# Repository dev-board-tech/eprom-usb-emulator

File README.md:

# eprom-usb-emulator
 A USB EPROM EEPROM RAM emulator

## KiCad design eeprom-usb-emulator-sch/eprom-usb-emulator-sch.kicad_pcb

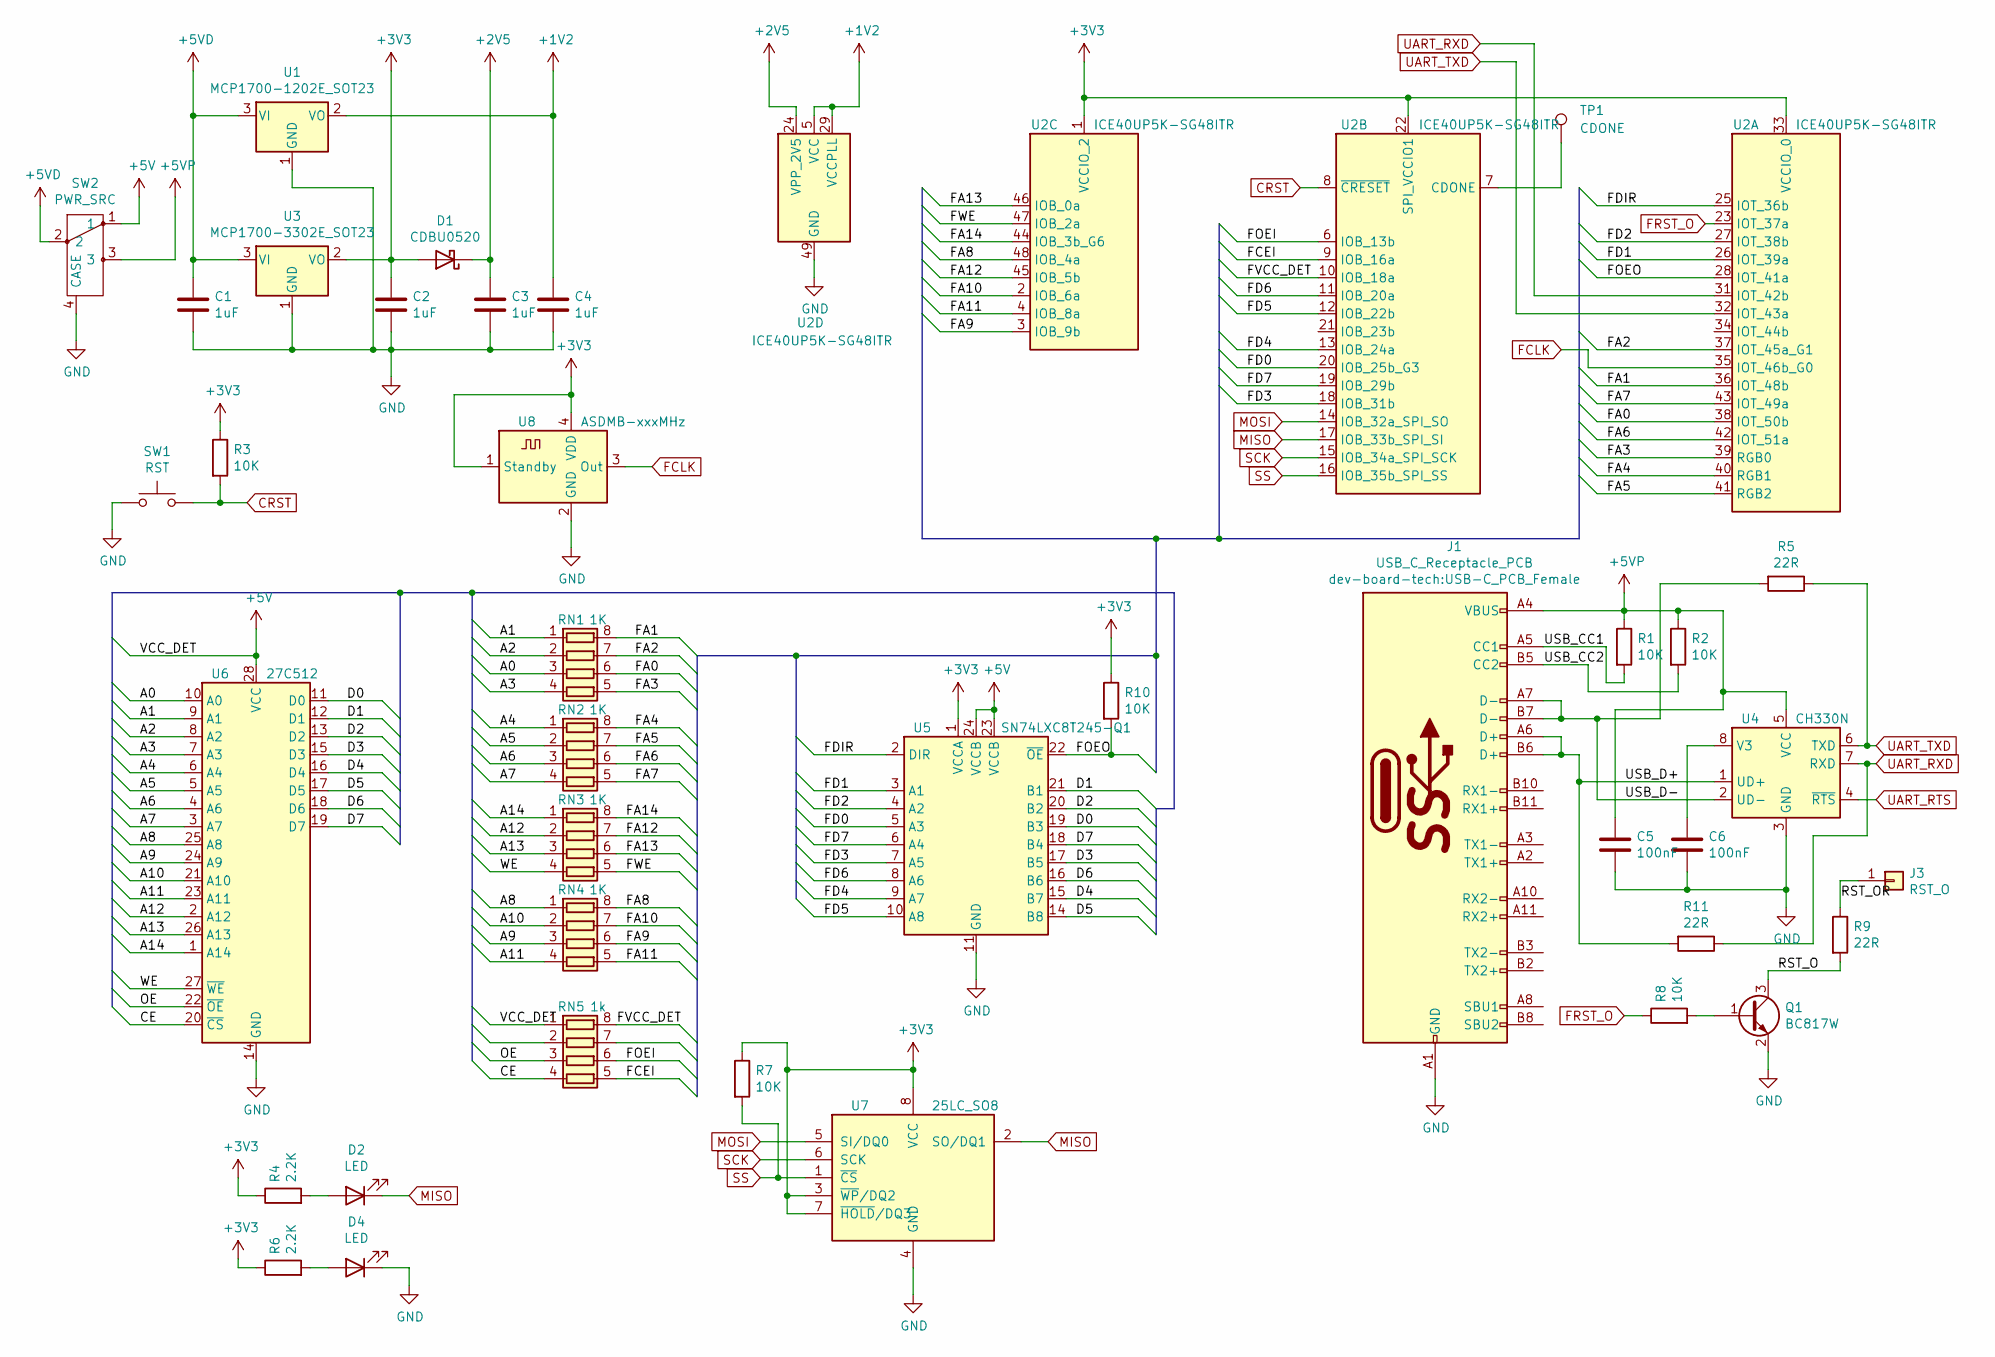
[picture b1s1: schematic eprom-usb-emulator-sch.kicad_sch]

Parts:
C1, C2, C3, C4: 1uF; C_0805_2012Metric
C5, C6: 100nF; C_0603_1608Metric
D1: CDBU0520; D_SOD-523
D2, D4: LED; LED_0603_1608Metric
J1: USB_C_Receptacle_PCB; USB-C_PCB_Female
J3: RST_O; PinHeader_1x01_P2.54mm_Vertical
Q1: BC817W; SOT-323_SC-70
R1, R2, R3, R7, R8, R10: 10K; R_0603_1608Metric
R4, R6: 2.2K; R_0603_1608Metric
R5, R11: 22R; R_0402_1005Metric
R9: 22R; R_1206_3216Metric
RN1, RN2, RN3, RN4: 1K; R_Array_Convex_4x0402
RN5: 1k; R_Array_Convex_4x0402
SW1: RST; SW_SPST_CK_RS282G05A3
SW2: PWR_SRC; SW_SPDT_PCM12
TP1: CDONE; TestPoint_Pad_D1.0mm
U1: MCP1700-1202E_SOT23; SOT-23
U2: ICE40UP5K-SG48ITR; QFN-48-1EP_7x7mm_P0.5mm_EP5.6x5.6mm
U3: MCP1700-3302E_SOT23; SOT-23
U4: CH330N; SOIC-8_3.9x4.9mm_P1.27mm
U5: SN74LXC8T245-Q1; TSSOP-24_4.4x7.8mm_P0.65mm
U6: 27C512; 28PIN_EPROM_EMULATOR_DIP-28_W15.24mm
U7: 25LC_SO8; SOIC-8_3.9x4.9mm_P1.27mm
U8: ASDMB-xxxMHz; Oscillator_SMD_Abracon_ASDMB-4Pin_2.5x2.0mm

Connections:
+1V2: C4.1, U1.2 (VO), U2.5 (VCC), U2.29 (VCCPLL), U2.30 (VCC)
+2V5: C3.1, D1.1 (K), U2.24 (VPP_2V5)
+3V3: C2.1, D1.2 (A), R3.1, R4.1, R6.1, R7.1, R10.1, U2.1 (VCCIO_2), U2.22 (SPI_VCCIO1), U2.33 (VCCIO_0), U3.2 (VO), U5.1 (VCCA), U7.3 (~WP/DQ2), U7.7 (~HOLD/DQ3), U7.8 (VCC), U8.1 (Standby), U8.4 (VDD)
+5V: RN5.1 (R1.1), SW2.1, U5.23 (VCCB), U5.24 (VCCB), U6.28 (VCC)
+5VD: C1.1, SW2.2, U1.3 (VI), U3.3 (VI)
+5VP: C5.1, J1.A4 (VBUS), J1.A9 (VBUS), J1.B4 (VBUS), J1.B9 (VBUS), R1.1, R2.1, SW2.3, U4.5 (VCC)
/A0: RN1.3 (R3.1), U6.10 (A0)
/A1: RN1.1 (R1.1), U6.9 (A1)
/A2: RN1.2 (R2.1), U6.8 (A2)
/A3: RN1.4 (R4.1), U6.7 (A3)
/A4: RN2.1 (R1.1), U6.6 (A4)
/A5: RN2.2 (R2.1), U6.5 (A5)
/A6: RN2.3 (R3.1), U6.4 (A6)
/A7: RN2.4 (R4.1), U6.3 (A7)
/A8: RN4.1 (R1.1), U6.25 (A8)
/A9: RN4.3 (R3.1), U6.24 (A9)
/A10: RN4.2 (R2.1), U6.21 (A10)
/A11: RN4.4 (R4.1), U6.23 (A11)
/A12: RN3.2 (R2.1), U6.2 (A12)
/A13: RN3.3 (R3.1), U6.26 (A13)
/A14: RN3.1 (R1.1), U6.1 (A14)
/CE: RN5.4 (R4.1), U6.20 (~CS)
/D0: U5.19 (B3), U6.11 (D0)
/D1: U5.21 (B1), U6.12 (D1)
/D2: U5.20 (B2), U6.13 (D2)
/D3: U5.17 (B5), U6.15 (D3)
/D4: U5.15 (B7), U6.16 (D4)
/D5: U5.14 (B8), U6.17 (D5)
/D6: U5.16 (B6), U6.18 (D6)
/D7: U5.18 (B4), U6.19 (D7)
/FA0: RN1.6 (R3.2), U2.38 (IOT_50b)
/FA1: RN1.8 (R1.2), U2.36 (IOT_48b)
/FA2: RN1.7 (R2.2), U2.37 (IOT_45a_G1)
/FA3: RN1.5 (R4.2), U2.39 (RGB0)
/FA4: RN2.8 (R1.2), U2.40 (RGB1)
/FA5: RN2.7 (R2.2), U2.41 (RGB2)
/FA6: RN2.6 (R3.2), U2.42 (IOT_51a)
/FA7: RN2.5 (R4.2), U2.43 (IOT_49a)
/FA8: RN4.8 (R1.2), U2.48 (IOB_4a)
/FA9: RN4.6 (R3.2), U2.3 (IOB_9b)
/FA10: RN4.7 (R2.2), U2.2 (IOB_6a)
/FA11: RN4.5 (R4.2), U2.4 (IOB_8a)
/FA12: RN3.7 (R2.2), U2.45 (IOB_5b)
/FA13: RN3.6 (R3.2), U2.46 (IOB_0a)
/FA14: RN3.8 (R1.2), U2.44 (IOB_3b_G6)
/FCEI: RN5.5 (R4.2), U2.9 (IOB_16a)
/FD0: U2.20 (IOB_25b_G3), U5.5 (A3)
/FD1: U2.26 (IOT_39a), U5.3 (A1)
/FD2: U2.27 (IOT_38b), U5.4 (A2)
/FD3: U2.18 (IOB_31b), U5.7 (A5)
/FD4: U2.13 (IOB_24a), U5.9 (A7)
/FD5: U2.12 (IOB_22b), U5.10 (A8)
/FD6: U2.11 (IOB_20a), U5.8 (A6)
/FD7: U2.19 (IOB_29b), U5.6 (A4)
/FDIR: U2.25 (IOT_36b), U5.2 (DIR)
/FOEI: RN5.6 (R3.2), U2.6 (IOB_13b)
/FOEO: R10.2, U2.28 (IOT_41a), U5.22 (~OE)
/FVCC_DET: RN5.8 (R1.2), U2.10 (IOB_18a)
/FWE: RN3.5 (R4.2), U2.47 (IOB_2a)
/OE: RN5.3 (R3.1), U6.22 (~OE)
/RST_O: Q1.3 (C), R9.2
/RST_OR: J3.1, R9.1
/USB_CC1: J1.A5 (CC1), R1.2
/USB_CC2: J1.B5 (CC2), R2.2
/USB_D+: J1.A6 (D+), J1.B6 (D+), R11.2, U4.1 (UD+)
/USB_D-: J1.A7 (D-), J1.B7 (D-), R5.2, U4.2 (UD-)
/WE: RN3.4 (R4.1), U6.27 (~WE)
CRST: R3.2, SW1.2, U2.8 (~CRESET)
FCLK: U2.35 (IOT_46b_G0), U8.3 (Out)
FRST_O: R8.1, U2.23 (IOT_37a)
GND: C1.2, C2.2, C3.2, C4.2, C5.2, C6.2, D4.1 (K), J1.A1 (GND), J1.A12 (GND), J1.B1 (GND), J1.B12 (GND), Q1.2 (E), SW1.1, SW2.4 (CASE), SW2.5 (CASE), SW2.6 (CASE), SW2.7 (CASE), U1.1 (GND), U2.49 (GND), U3.1 (GND), U4.3 (GND), U5.11 (GND), U5.12 (GND), U5.13 (GND), U6.14 (GND), U7.4 (GND), U8.2 (GND)
MISO: D2.1 (K), U2.17 (IOB_33b_SPI_SI), U7.2 (SO/DQ1)
MOSI: U2.14 (IOB_32a_SPI_SO), U7.5 (SI/DQ0)
unnamed: D2.2 (A), R4.2
unnamed: D4.2 (A), R6.2
unnamed: Q1.1 (B), R8.2
unnamed: TP1.1, U2.7 (CDONE)
unnamed: C6.1, U4.8 (V3)
SCK: U2.15 (IOB_34a_SPI_SCK), U7.6 (SCK)
SS: R7.2, U2.16 (IOB_35b_SPI_SS), U7.1 (~CS)
UART_RTS: U4.4 (~RTS)
UART_RXD: R11.1, U2.31 (IOT_42b), U4.7 (RXD)
UART_TXD: R5.1, U2.32 (IOT_43a), U4.6 (TXD)

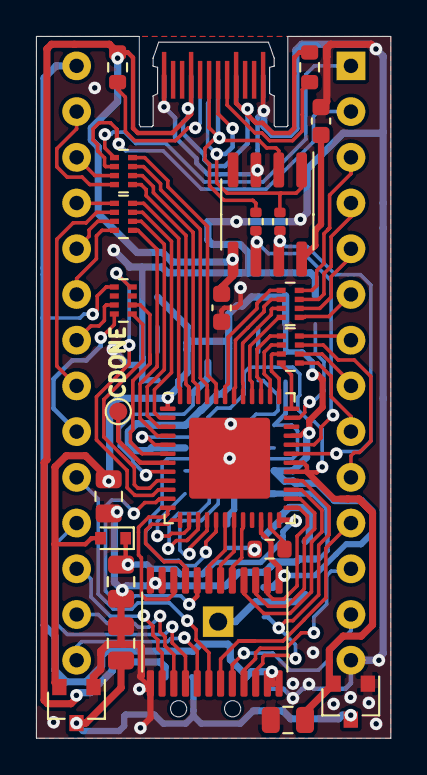
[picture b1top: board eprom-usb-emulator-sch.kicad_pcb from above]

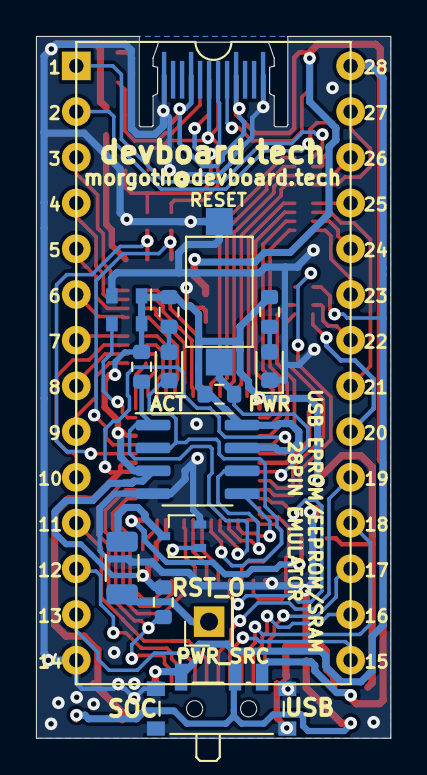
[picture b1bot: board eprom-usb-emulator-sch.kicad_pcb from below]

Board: 2 copper layers, 19.7 x 39.0 mm, 39 parts (15 on the bottom side), 82 nets.

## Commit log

2024-04-05 First releae
2024-04-05 Add schematic PDF and update presentation image
2026-04-29 Update!
